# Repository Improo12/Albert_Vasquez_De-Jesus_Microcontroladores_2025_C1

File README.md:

# Albert_Vasquez_De-Jesus_Microcontroladores_2025_C1

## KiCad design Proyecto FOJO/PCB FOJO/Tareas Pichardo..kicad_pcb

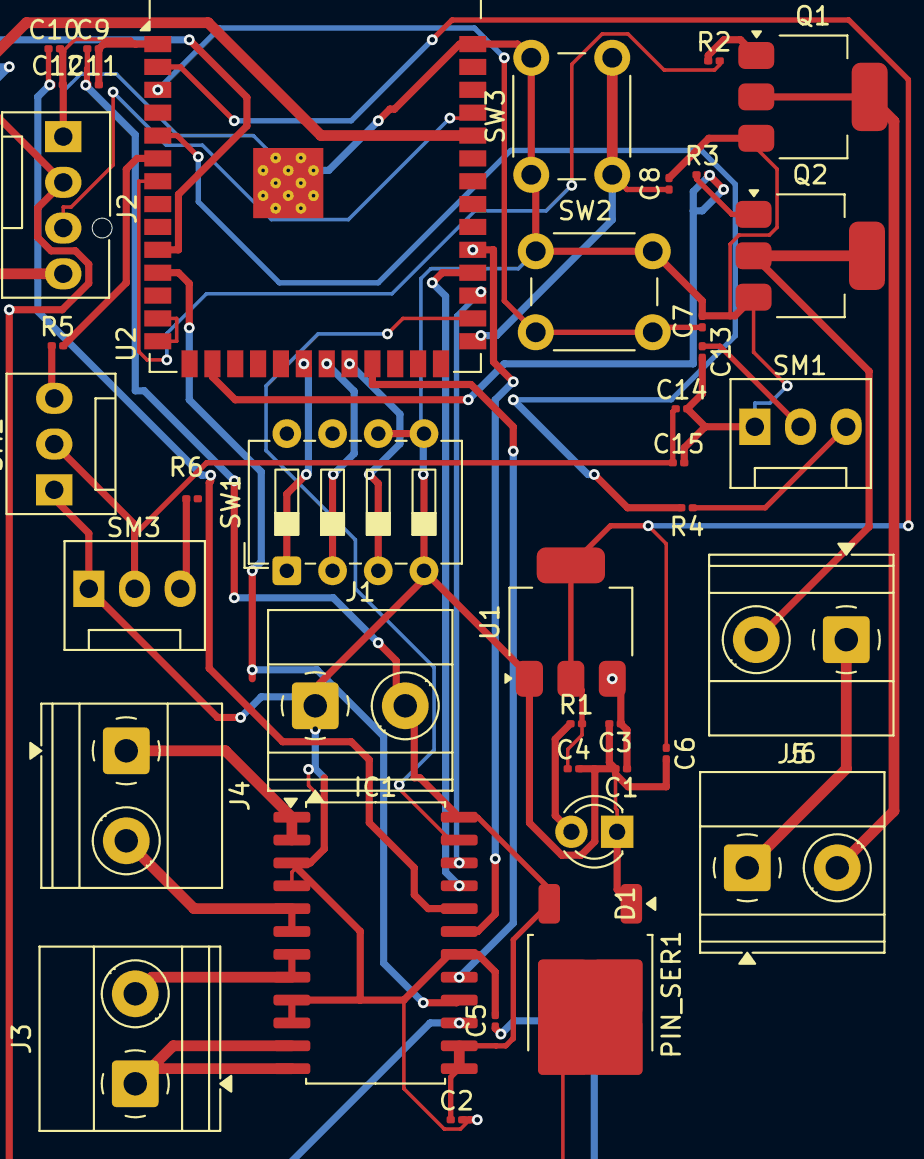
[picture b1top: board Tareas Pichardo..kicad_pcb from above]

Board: 2 copper layers, 40 parts (0 on the bottom side), 40 nets.

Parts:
C1, C2, C3, C4, C5, C6, C7, C8, C9, C10: 0.1uf; C_0201_0603Metric
C11, C12: 10uf; C_0201_0603Metric
C13, C14, C15: 470uf; C_0201_0603Metric
D1: LED; LED_D3.0mm
IC1: TB6612FNG,C,8,EL; SOIC-24W_7.5x15.4mm_P1.27mm
J1: Screw_Terminal_01x02; TerminalBlock_Phoenix_MKDS-1,5-2_1x02_P5.00mm_Horizontal
J2: Conn_01x04_Pin; FanPinHeader_1x04_P2.54mm_Vertical
J3: MOTOT 1; TerminalBlock_Phoenix_MKDS-1,5-2_1x02_P5.00mm_Horizontal
J4: MOTOR2; TerminalBlock_Phoenix_MKDS-1,5-2_1x02_P5.00mm_Horizontal
J5: LAMP; TerminalBlock_Phoenix_MKDS-1,5-2_1x02_P5.00mm_Horizontal
J6: BZ; TerminalBlock_Phoenix_MKDS-1,5-2_1x02_P5.00mm_Horizontal
PIN_SER1: AZ1117D-ADJ; TO-252-2
Q1, Q2: PZT2222A; SOT-223-3_TabPin2
R1: R; R_0201_0603Metric
R2, R3: 1K; R_0201_0603Metric
R4, R5, R6: 330; R_0201_0603Metric
SM1, SM2, SM3: Conn_01x03_Pin; FanPinHeader_1x03_P2.54mm_Vertical
SW1: SW_DIP_x03; SW_DIP_SPSTx04_Slide_6.7x11.72mm_W7.62mm_P2.54mm_LowProfile
SW2, SW3: SW_Push; SW_PUSH_6mm_H7.3mm
U1: AMS1117-3.3; SOT-223-3_TabPin2
U2: ESP32-S3-WROOM-1

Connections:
+3.3V: C4.1, C6.1, R1.2, U1.2 (VO), U2.2 (3V3)
+5: C5.1, J2.2, PIN_SER1.2 (VO)
AIN1: IC1.21 (AIN1), U2.30 (IO37)
AIN2: IC1.22 (AIN2), U2.29 (IO36)
BIN1: IC1.17 (BIN1), U2.23 (IO21)
BIN2: IC1.16 (BIN2), U2.11 (IO18)
BT: C8.1, SW3.2, U2.27 (IO0)
BZ: R3.2, U2.16 (IO46)
EN: C7.1, SW2.2, U2.3 (EN)
GND: C1.2, C2.2, C3.2, C4.2, C5.2, C6.2, C7.2, C8.2, C9.2, C10.2, C11.2, C12.2, C13.2, C14.2, C15.2, D1.1 (K), IC1.3 (PGND1_1), IC1.4 (PGND1_2), IC1.9 (PGND2_1), IC1.10 (PGND2_2), IC1.18 (GND), J1.1, J2.1, PIN_SER1.1 (ADJ), Q1.3 (E), Q2.3 (E), SM1.1, SM2.1, SM3.1, SW1.4, SW1.5, SW1.6, SW2.1, SW3.1, U1.1 (GND), U2.1 (GND), U2.40 (GND), U2.41 (GND)
LAMP: R2.2, U2.7 (IO7)
MA1: IC1.1 (AO1_1), IC1.2 (AO1_2), J4.1
MA2: IC1.5 (AO2_1), IC1.6 (AO2_2), J4.2
MB1: IC1.11 (BO1_1), IC1.12 (BO1_2), J3.1
MB2: IC1.7 (BO2_1), IC1.8 (BO2_2), J3.2
unnamed: D1.2 (A), R1.1
unnamed: C10.1, C12.1, IC1.20 (VCC)
unnamed: J5.2, Q1.2 (C)
unnamed: J6.2, Q2.2 (C)
unnamed: Q1.1 (B), R2.1
unnamed: Q2.1 (B), R3.1
unnamed: R4.1, SM1.3
unnamed: R5.1, SM2.3
unnamed: R6.1, SM3.3
unnamed: C1.1, C3.1, U1.3 (VI)
PIN_DIP1: SW1.1, U2.20 (IO12)
PIN_DIP2: SW1.2, U2.21 (IO13)
PIN_DIP3: SW1.3, U2.22 (IO14)
PIN_SERV01: R4.2, U2.5 (IO5)
PIN_SERV02: R5.2, U2.6 (IO6)
PWMA: IC1.23 (PWMA), U2.28 (IO35)
PWMB: IC1.15 (PWMB), U2.10 (IO17)
RX: J2.4, U2.36 (RXD0)
STBY: IC1.19 (STBY), U2.31 (IO38)
TX: J2.3, U2.37 (TXD0)
VIN: C2.1, C9.1, C11.1, IC1.13 (VM2), IC1.14 (VM3), IC1.24 (VM1), J1.2, PIN_SER1.3 (VI)
VIN-SERVO: J5.1, J6.1
VIN_SERV0: C14.1, C15.1, SM2.2, SM3.2
VIN_SERV02: C13.1, SM1.2
X: U2.13 (USB_D-), U2.14 (USB_D+)

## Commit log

2025-04-26 Create prueba.txt
    Prueba
2025-04-26 Create main.c
    Maquina de estado
2025-04-26 Comando de Git
2025-04-26 Proyecto Emulador 555
2025-04-26 Proyecto final
    Emulador 555
2025-04-26 Tarea 5
    Trea 5
2025-04-30 Proyecto Fojo
    FOJO
